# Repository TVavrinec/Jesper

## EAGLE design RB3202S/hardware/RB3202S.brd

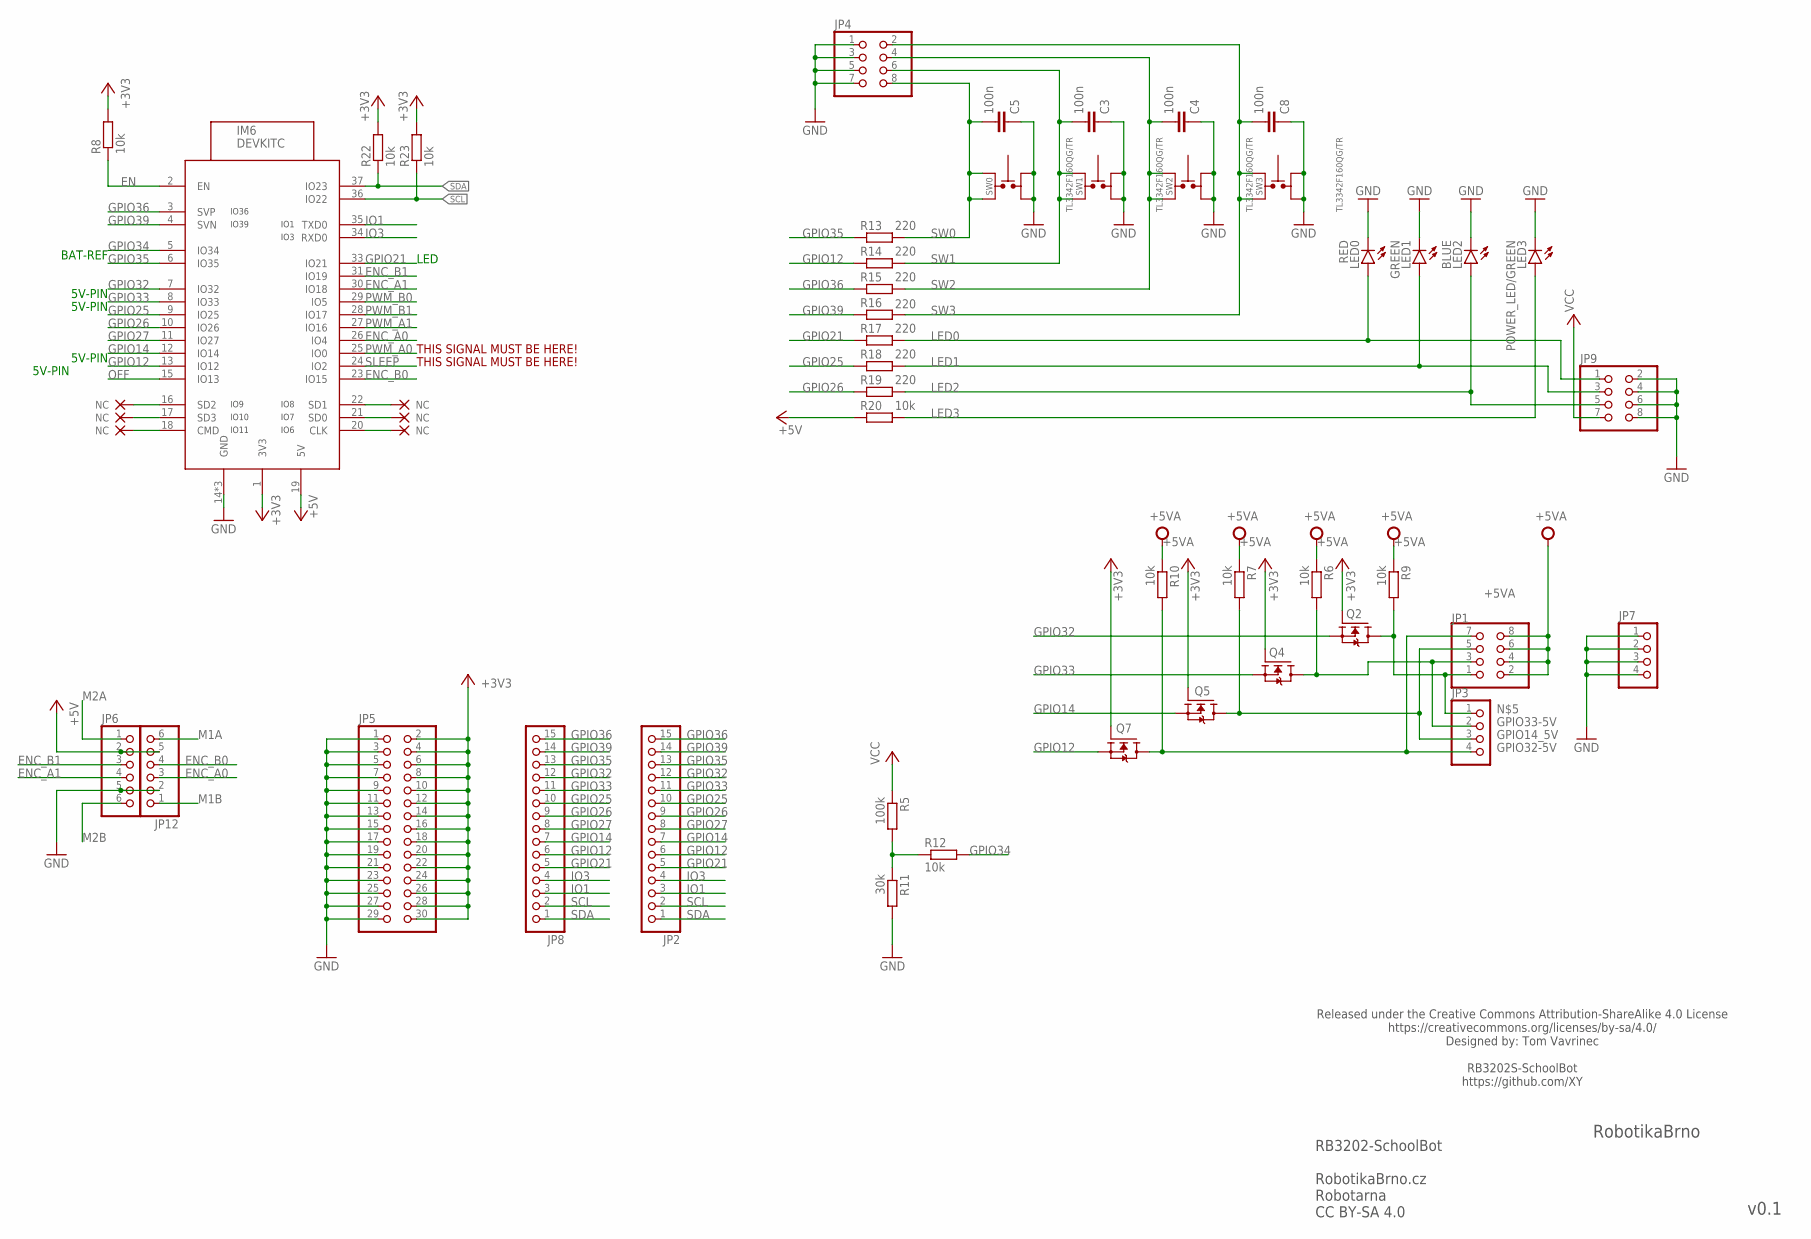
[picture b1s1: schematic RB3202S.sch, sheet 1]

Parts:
C3, C4, C5, C8: 100n; C0402
IM6: DEVKITC
JP1, JP4, JP9: PINHD-2X4; 2X04
JP2, JP8: PINHD-1X15; 1X15
JP3, JP7: PINHD-1X4; 1X04
JP5: PINHD-2X15; 2X15
JP6, JP12: PINHD-1X6; 1X06
LED0: RED; SML0603
LED1: GREEN; SML0603
LED2: BLUE; SML0603
LED3: POWER_LED/GREEN; SML0603
Q2, Q4, Q5, Q7: N-MOSFET-SOT23-GSD; SOT23
R5: 100k; R0402
R6, R7, R8, R9, R10, R12, R20, R22, R23: 10k; R0402
R11: 30k; R0402
R13, R14, R15, R16, R17, R18, R19: 220; R0402
SW0, SW1, SW2, SW3: TL3342F160QG/TR

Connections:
+3V3: IM6.1 (3V3), JP5.2, JP5.4, JP5.6, JP5.8, JP5.10, JP5.12, JP5.14, JP5.16, JP5.18, JP5.20, JP5.22, JP5.24, JP5.26, JP5.28, JP5.30, Q2.1 (G), Q4.1 (G), Q5.1 (G), Q7.1 (G), R8.2, R22.2, R23.2; also elsewhere on the board
+5V: IM6.19 (5V), JP6.2, JP12.5, R20.1; also elsewhere on the board
+5VA: JP1.2, JP1.4, JP1.6, JP1.8, R6.1, R7.1, R9.1, R10.1; also elsewhere on the board
EN: IM6.2 (EN), R8.1; also elsewhere on the board
ENC_A0: IM6.26 (IO4), JP12.3
ENC_A1: IM6.30 (IO18), JP6.4
ENC_B0: IM6.23 (IO15), JP12.4
ENC_B1: IM6.31 (IO19), JP6.3
GND: C3.1, C4.1, C5.1, C8.1, IM6.14 (GND), IM6.32 (GND), IM6.38 (GND), JP4.1, JP4.3, JP4.5, JP4.7, JP5.1, JP5.3, JP5.5, JP5.7, JP5.9, JP5.11, JP5.13, JP5.15, JP5.17, JP5.19, JP5.21, JP5.23, JP5.25, JP5.27, JP5.29, JP6.5, JP7.1, JP7.2, JP7.3, JP7.4, JP9.2, JP9.4, JP9.6, JP9.8, JP12.2, LED0.C, LED1.C, LED2.C, LED3.C, R11.2, SW0.1, SW0.2, SW1.1, SW1.2, SW2.1, SW2.2, SW3.1, SW3.2; also elsewhere on the board
GPIO12: IM6.13 (IO12), JP2.6, JP8.6, Q7.2 (S), R14.1
GPIO14: IM6.12 (IO14), JP2.7, JP8.7, Q5.2 (S)
GPIO14_5V: JP1.5, JP3.3, Q5.3 (D), R7.2
GPIO21: IM6.33 (IO21), JP2.5, JP8.5, R17.1; also elsewhere on the board
GPIO25: IM6.9 (IO25), JP2.10, JP8.10, R18.1
GPIO26: IM6.10 (IO26), JP2.9, JP8.9, R19.1
GPIO27: IM6.11 (IO27), JP2.8, JP8.8; also elsewhere on the board
GPIO32: IM6.7 (IO32), JP2.12, JP8.12, Q2.2 (S)
GPIO32-5V: JP1.7, JP3.4, Q7.3 (D), R10.2
GPIO33: IM6.8 (IO33), JP2.11, JP8.11, Q4.2 (S)
GPIO33-5V: JP1.3, JP3.2, Q4.3 (D), R6.2
GPIO34: IM6.5 (IO34), R12.2
GPIO35: IM6.6 (IO35), JP2.13, JP8.13, R13.1
GPIO36: IM6.3 (SVP), JP2.15, JP8.15, R15.1; also elsewhere on the board
GPIO39: IM6.4 (SVN), JP2.14, JP8.14, R16.1; also elsewhere on the board
IO1: IM6.35 (TXD0), JP2.3, JP8.3
IO3: IM6.34 (RXD0), JP2.4, JP8.4
IO9_NC: IM6.16 (SD2)
IO9_NC1: IM6.20 (CLK)
IO10_NC: IM6.17 (SD3)
IO10_NC1: IM6.21 (SD0)
IO11_NC: IM6.18 (CMD)
IO11_NC1: IM6.22 (SD1)
LED0: JP9.1, LED0.A, R17.2
LED1: JP9.3, LED1.A, R18.2
LED2: JP9.5, LED2.A, R19.2
LED3: LED3.A, R20.2
M1A: JP12.6; also elsewhere on the board
M1B: JP12.1; also elsewhere on the board
M2A: JP6.1; also elsewhere on the board
M2B: JP6.6; also elsewhere on the board
unnamed: R5.2, R11.1, R12.1
unnamed: JP1.1, JP3.1, Q2.3 (D), R9.2
OFF: IM6.15 (IO13); also elsewhere on the board
PWM_A0: IM6.25 (IO0); also elsewhere on the board
PWM_A1: IM6.27 (IO16); also elsewhere on the board
PWM_B0: IM6.29 (IO5); also elsewhere on the board
PWM_B1: IM6.28 (IO17); also elsewhere on the board
SCL: IM6.36 (IO22), JP2.2, JP8.2, R23.1; also elsewhere on the board
SDA: IM6.37 (IO23), JP2.1, JP8.1, R22.1; also elsewhere on the board
SLEEP: IM6.24 (IO2); also elsewhere on the board
SW0: C5.2, JP4.8, R13.2, SW0.3, SW0.4
SW1: C3.2, JP4.6, R14.2, SW1.3, SW1.4
SW2: C4.2, JP4.4, R15.2, SW2.3, SW2.4
SW3: C8.2, JP4.2, R16.2, SW3.3, SW3.4
VCC: JP9.7, R5.1; also elsewhere on the board

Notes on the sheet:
RB3202-SchoolBot RobotikaBrno.cz Robotarna CC BY-SA 4.0
RobotikaBrno
v0.1
Released under the Creative Commons Attribution-ShareAlike 4.0 License https://creativecommons.org/licenses/by-sa/4.0/ Designed by: Tom Vavrinec RB3202S-SchoolBot https://github.com/XY
THIS SIGNAL MUST BE HERE!
LED
5V-PIN
BAT-REF

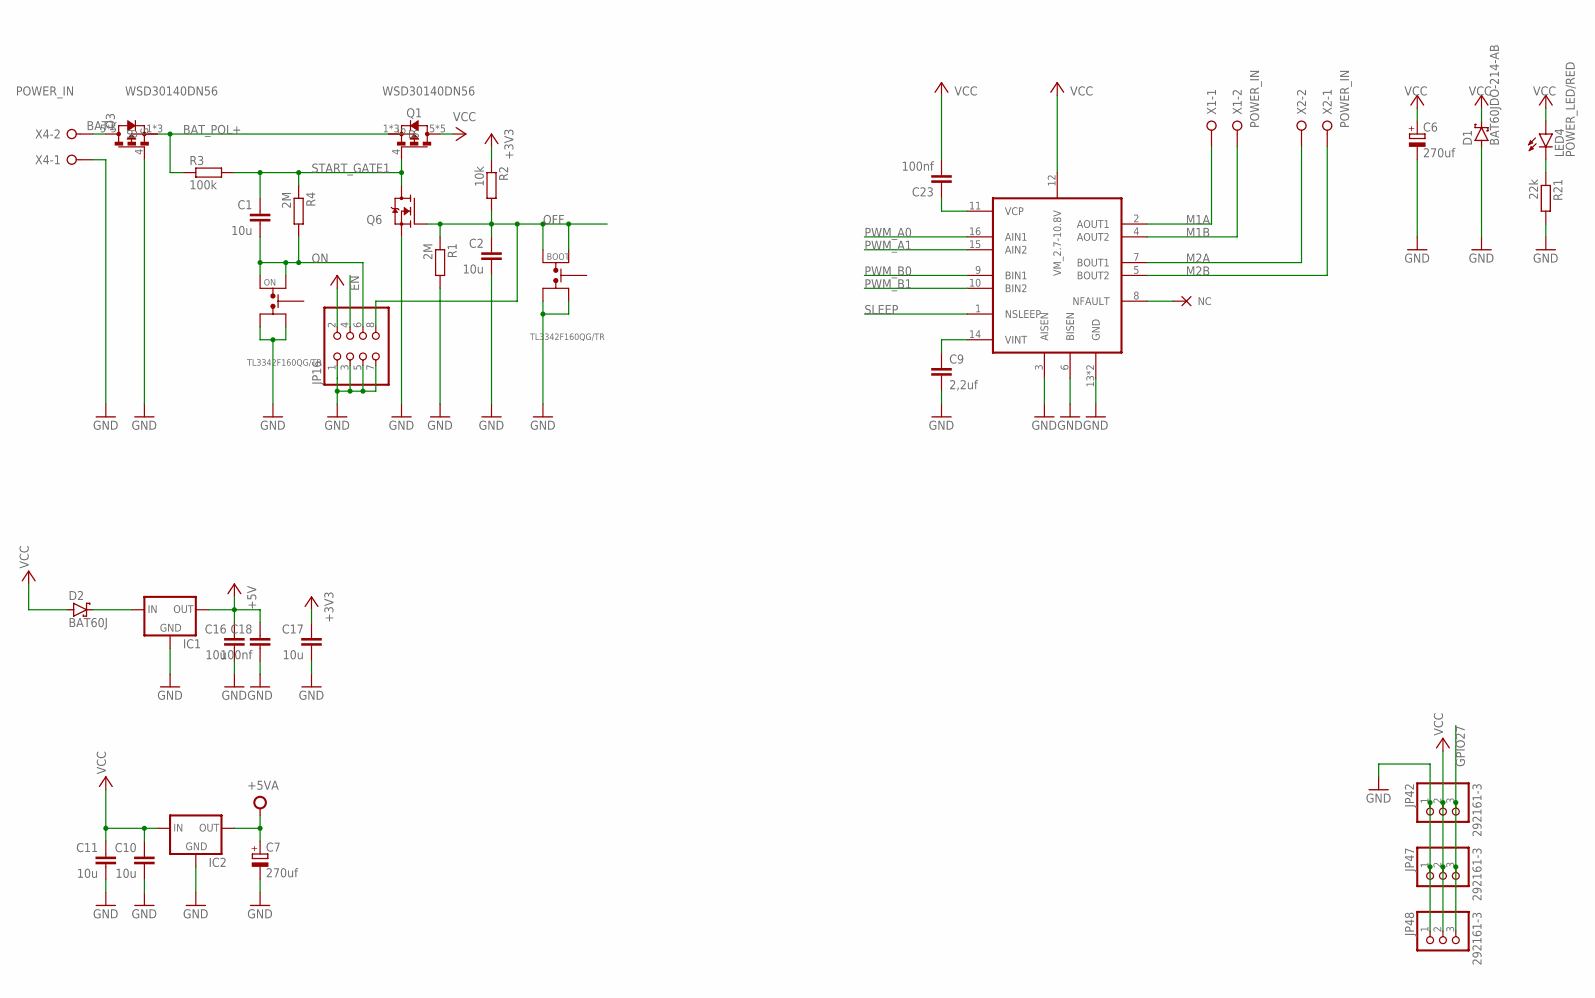
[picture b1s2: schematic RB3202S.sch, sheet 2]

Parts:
BOOT: TL3342F160QG/TR
C1, C2, C10, C11, C16, C17: 10u; C1206
C6, C7: 270uf; 140CLH-1010
C9: 2,2uf; C0805
C18: 100nf; C1206
C23: 100nf; C0402
D1: BAT60JDO-214-AB; DO214BA
D2: BAT60J; SOD323_ST
IC1, IC2: LM1117; SOT223
JP16: PINHD-2X4; 2X04
JP42, JP47, JP48: 292161-3
LED4: POWER_LED/RED; SML0603
ON: TL3342F160QG/TR
Q1, Q3: WSD30140DN56; DFN-8_EP_5.2X6.0X1.27P
Q6: N-MOSFET-SOT23-GSD; SOT23
R1, R4: 2M; R0402
R2: 10k; R0402
R3: 100k; R0402
R21: 22k; R0402
U$9: DRV8833CPWPR; SOP65P640X120-17N
X1, X2, X4: POWER_IN; W237-132

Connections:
+3V3: C17.1, R2.1; also elsewhere on the board
+5V: C16.1, C18.1, IC1.2 (OUT), IC1.4 (OUT), JP16.2; also elsewhere on the board
+5VA: C7.+, IC2.2 (OUT), IC2.4 (OUT); also elsewhere on the board
BAT1: Q3.5 (D), Q3.6 (D), Q3.7 (D), Q3.8 (D), Q3.9 (D), X4.2
BAT_POL+: Q1.1 (S), Q1.2 (S), Q1.3 (S), Q3.1 (S), Q3.2 (S), Q3.3 (S), R3.1
EN: JP16.4; also elsewhere on the board
GND: BOOT.1, BOOT.2, C2.2, C6.-, C7.-, C9.2, C10.2, C11.2, C16.2, C17.2, C18.2, D1.A, IC1.1 (GND), IC2.1 (GND), JP16.1, JP16.3, JP16.5, JP16.7, JP42.1, JP47.1, JP48.1, ON.1, ON.2, Q3.4 (G), Q6.2 (S), R1.2, R21.2, U$9.3 (AISEN), U$9.6 (BISEN), U$9.13 (GND), U$9.17 (GND), X4.1; also elsewhere on the board
GPIO27: JP42.3, JP47.3, JP48.3; also elsewhere on the board
IO9_NC2: U$9.8 (NFAULT)
M1A: U$9.2 (AOUT1), X1.1; also elsewhere on the board
M1B: U$9.4 (AOUT2), X1.2; also elsewhere on the board
M2A: U$9.7 (BOUT1), X2.2; also elsewhere on the board
M2B: U$9.5 (BOUT2), X2.1; also elsewhere on the board
unnamed: LED4.C, R21.1
unnamed: D2.C, IC1.3 (IN)
unnamed: C9.1, U$9.14 (VINT)
unnamed: C23.1, U$9.11 (VCP)
OFF: BOOT.3, BOOT.4, C2.1, JP16.8, Q6.1 (G), R1.1, R2.2; also elsewhere on the board
ON: C1.2, JP16.6, ON.3, ON.4, R4.2
PWM_A0: U$9.16 (AIN1); also elsewhere on the board
PWM_A1: U$9.15 (AIN2); also elsewhere on the board
PWM_B0: U$9.9 (BIN1); also elsewhere on the board
PWM_B1: U$9.10 (BIN2); also elsewhere on the board
SLEEP: U$9.1 (NSLEEP); also elsewhere on the board
START_GATE1: C1.1, Q1.4 (G), Q6.3 (D), R3.2, R4.1
VCC: C6.+, C10.1, C11.1, C23.2, D1.C, D2.A, IC2.3 (IN), JP42.2, JP47.2, JP48.2, LED4.A, Q1.5 (D), Q1.6 (D), Q1.7 (D), Q1.8 (D), Q1.9 (D), U$9.12 (VM_2.7-10.8V); also elsewhere on the board

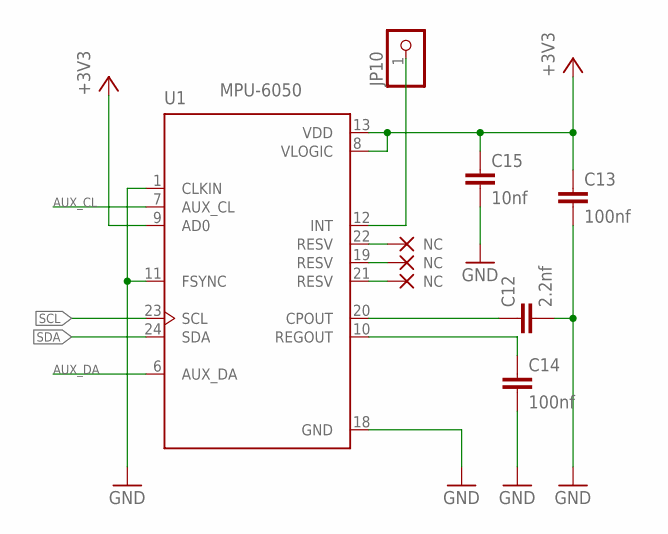
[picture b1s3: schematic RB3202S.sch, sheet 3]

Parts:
C12: 2.2nf; C0402
C13: 100nf; C0402
C14: 100nf; C0402P
C15: 10nf; C0402
JP10: PINHD-1X1; 1X01
U1: MPU-6050; QFN50P400X400X95-24N

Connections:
+3V3: C13.1, C15.1, U1.8 (VLOGIC), U1.9 (AD0), U1.13 (VDD); also elsewhere on the board
AUX_CL: U1.7 (AUX_CL)
AUX_DA: U1.6 (AUX_DA)
GND: C12.2, C13.2, C14.2, C15.2, U1.1 (CLKIN), U1.11 (FSYNC), U1.18 (GND); also elsewhere on the board
INT_MPU5060: JP10.1, U1.12 (INT)
IO9_NC4: U1.19 (RESV)
IO9_NC5: U1.21 (RESV)
IO10_NC4: U1.22 (RESV)
unnamed: C12.1, U1.20 (CPOUT)
unnamed: C14.1, U1.10 (REGOUT)
SCL: U1.23 (SCL); also elsewhere on the board
SDA: U1.24 (SDA); also elsewhere on the board

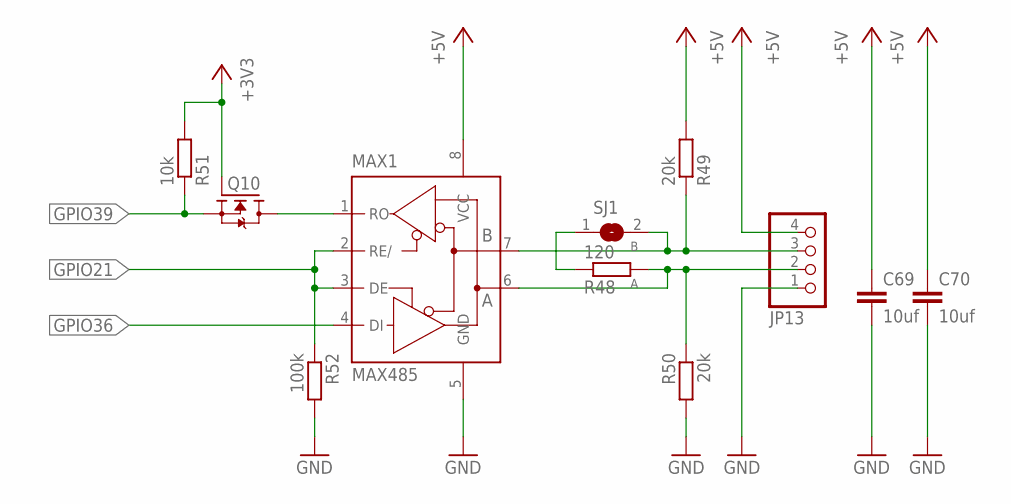
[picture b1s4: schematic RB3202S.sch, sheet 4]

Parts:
C69, C70: 10uf; C0805
JP13: PINHD-1X4; 1X04
MAX1: MAX485; SO08
Q10: N-MOSFET-SOT23-GSD; SOT23
R48: 120; R0402
R49, R50: 20k; R0402
R51: 10k; R0402
R52: 100k; R0402
SJ1: SJ

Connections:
+3V3: Q10.1 (G), R51.2; also elsewhere on the board
+5V: C69.1, C70.1, JP13.4, MAX1.8 (VCC), R49.2; also elsewhere on the board
A: JP13.2, MAX1.6 (A), R48.2, R50.1
B: JP13.3, MAX1.7 (B), R49.1, SJ1.2
GND: C69.2, C70.2, JP13.1, MAX1.5 (GND), R50.2, R52.2; also elsewhere on the board
GPIO21: MAX1.2 (RE/), MAX1.3 (DE), R52.1; also elsewhere on the board
GPIO36: MAX1.4 (DI); also elsewhere on the board
GPIO39: Q10.2 (S), R51.1; also elsewhere on the board
unnamed: R48.1, SJ1.1
RX-485-5V: MAX1.1 (RO), Q10.3 (D)

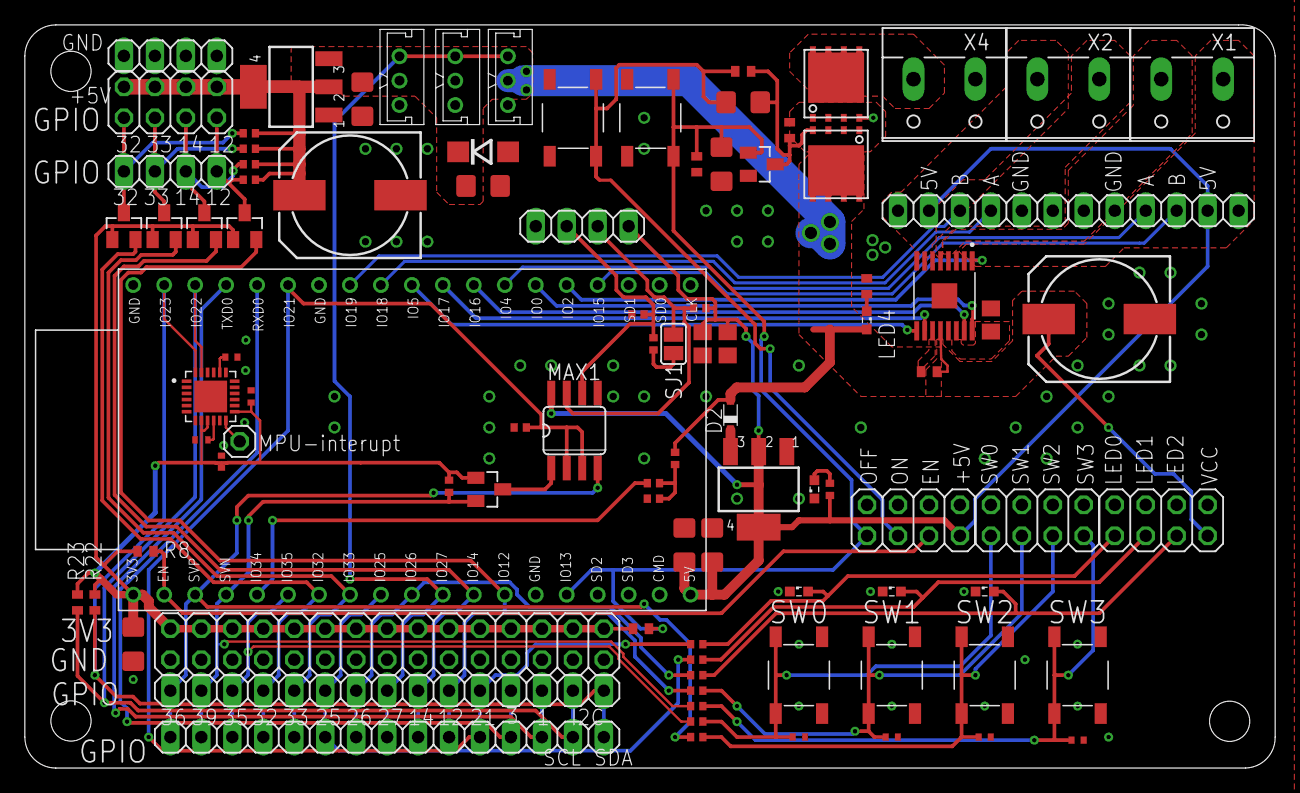
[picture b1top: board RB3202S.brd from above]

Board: 2 copper layers, 102.6 x 61.0 mm, 96 parts (0 on the bottom side), 64 nets.

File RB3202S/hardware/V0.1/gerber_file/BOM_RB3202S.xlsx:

Comment | Designator | Footprint | LCSC Part #（optional）
 | IC1, IC2 | SOT-223 | C134077
270uf | C6, C7 | SMD-ECAP-10x10 | C311670
100nf | C3, C4, C5, C8, C13, C14, C20, C21, C23 | 0402_C | C1525
10uf | C1, C2, C10, C11, C16, C17 | 1206_C | C89632
10uf | C69, C70 | 0805_C | C15850
2.2uf | C9 | 0805_C | C49217
2.2nf | C12 | 0402_C | C1531
220nf | C18 | 0402_C | C16772
4.7uf | C19 | 0805_C | C1779
10nf | C15 | 0402_C | C15195
 | D1 | DO214BA | C110482
 | LED0, LED4 | LED_0603 | C2286
 | LED2, LED3 | LED_0603 | C72043
 | LED1 | LED_0603 | C72038
 | SW0, SW1, SW2, SW3, ON, BOOT | TL3342F160QG/TR | C318887
 | Q1, Q3 | AO3401ASOP-8_EP_5.0X5.0X1.27P | C180399
 | Q2, Q4, Q5, Q6, Q7, Q10 | SOT-23-3 | C122850
 | U$9 | HTSSOP-16_EP_4.4x5.0x0.65P | C50506
 | U1 | QFN-24_EP_4.0x4.0x0.5P | C24112
1M | R1, R4 | 0402_R | C26083
10k | R2, R6, R7, R8, R9, 10, R12, R22, R23, R51 | 0402_R | C25744
100k | R3, R52 | 0402_R | C25741
100k | R5, R49 | 0402_R | C25741
30k | R11, R50 | 0402_R | C105614
120 | R48 | 0402_R | C25079
220 | R13-19 | 0402_R | C25092
1k | R20, R21 | 0402_R | C11702
 | IC3 | LGA-16_3x3x0.5P | C192585
 | MAX1 | SOIC-8_3.9x4.9x1.27P | C9945

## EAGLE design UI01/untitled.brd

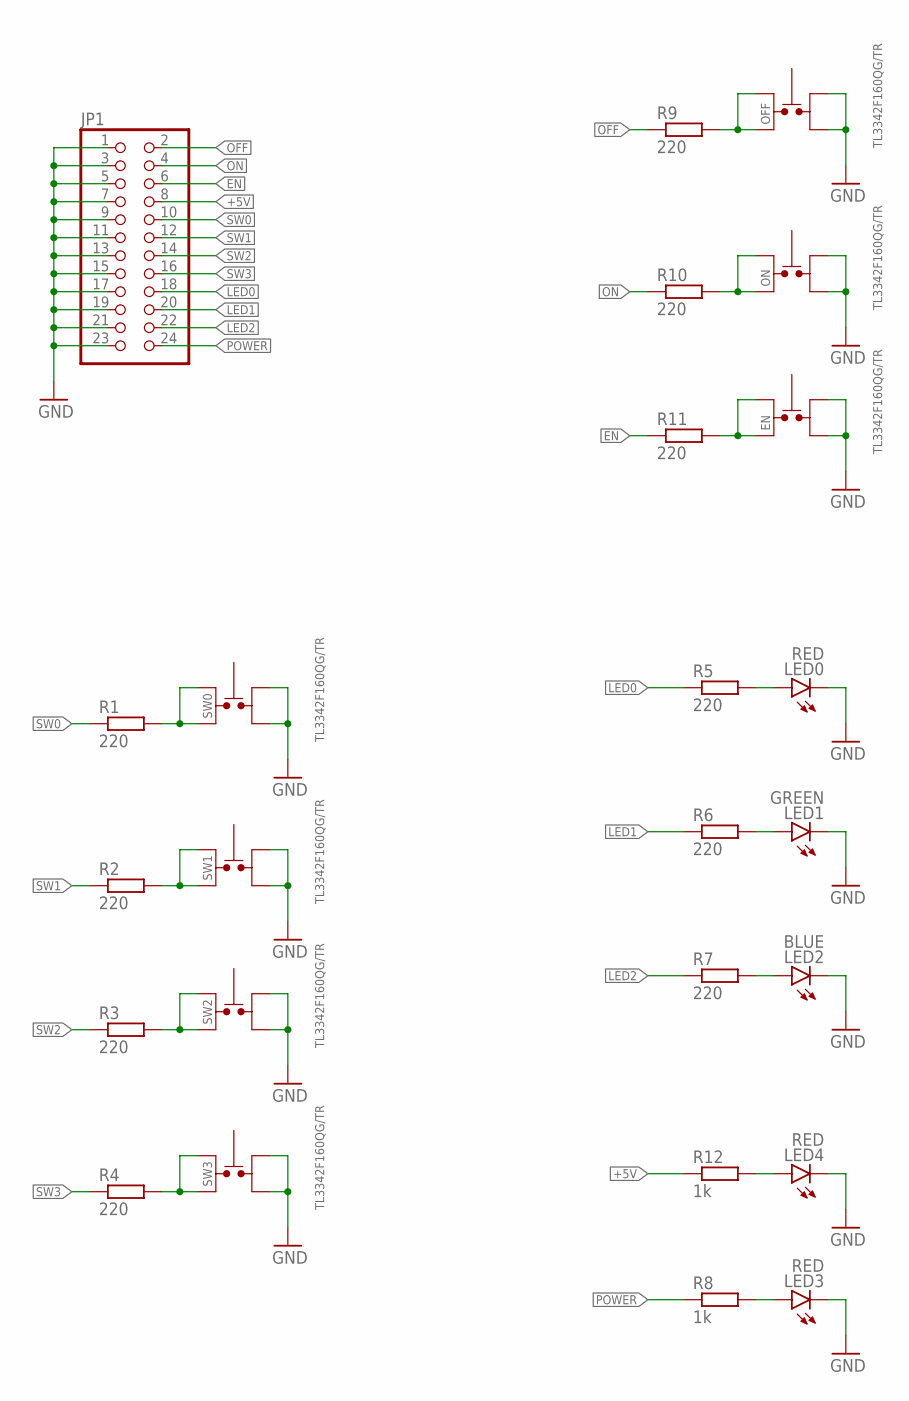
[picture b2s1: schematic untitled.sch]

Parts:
EN: TL3342F160QG/TR
JP1: PINHD-2X12; 2X12
LED0, LED3, LED4: RED; SML0603
LED1: GREEN; SML0603
LED2: BLUE; SML0603
OFF: TL3342F160QG/TR
ON: TL3342F160QG/TR
R1, R2, R3, R4, R5, R6, R7, R9, R10, R11: 220; R0402
R8, R12: 1k; R0402
SW0, SW1, SW2, SW3: TL3342F160QG/TR

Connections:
+5V: JP1.8, R12.1
EN: JP1.6, R11.1
GND: EN.1, EN.2, JP1.1, JP1.3, JP1.5, JP1.7, JP1.9, JP1.11, JP1.13, JP1.15, JP1.17, JP1.19, JP1.21, JP1.23, LED0.C, LED1.C, LED2.C, LED3.C, LED4.C, OFF.1, OFF.2, ON.1, ON.2, SW0.1, SW0.2, SW1.1, SW1.2, SW2.1, SW2.2, SW3.1, SW3.2
LED0: JP1.18, R5.1
LED1: JP1.20, R6.1
LED2: JP1.22, R7.1
unnamed: R1.2, SW0.3, SW0.4
unnamed: R2.2, SW1.3, SW1.4
unnamed: R3.2, SW2.3, SW2.4
unnamed: R4.2, SW3.3, SW3.4
unnamed: LED0.A, R5.2
unnamed: LED1.A, R6.2
unnamed: LED2.A, R7.2
unnamed: LED3.A, R8.2
unnamed: OFF.3, OFF.4, R9.2
unnamed: ON.3, ON.4, R10.2
unnamed: EN.3, EN.4, R11.2
unnamed: LED4.A, R12.2
OFF: JP1.2, R9.1
ON: JP1.4, R10.1
POWER: JP1.24, R8.1
SW0: JP1.10, R1.1
SW1: JP1.12, R2.1
SW2: JP1.14, R3.1
SW3: JP1.16, R4.1

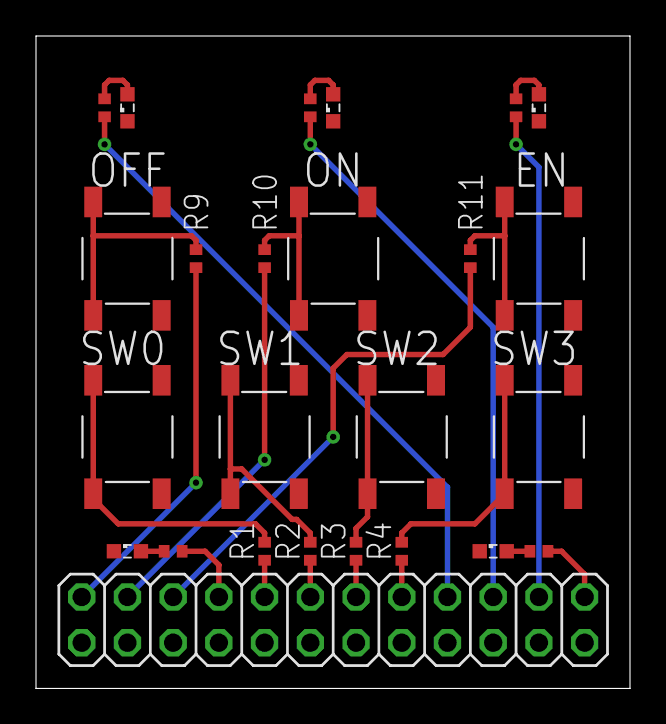
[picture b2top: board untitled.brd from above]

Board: 2 copper layers, 33.0 x 36.2 mm, 25 parts (0 on the bottom side), 25 nets.

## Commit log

2020-02-18 zaroutovana_deska
2020-02-20 kompas_navic
2020-03-01 loga
2020-03-10 BlackBox standard
2020-03-14 oprava ledek
2020-03-15 predelavka na ESP-IDF
2020-03-17 esp-idf
2020-05-02 dataasheety
2020-05-02 novi tranzistor do knihovny
    JLCPCB neměli ten starý na skladě tak jsem potřeboval jiný ale neměli ho ve stejném pouzdře tak jsem musel použít jiné
2020-05-02 zarazeni verze do jmena
2020-05-02 logo
2020-05-02 cisteni + gitignore
2020-05-02 aktualni nazvy
2020-05-02 nove logo
2020-05-02 libraris
2020-05-02 vyrova
    vytvoreni slozky pro verzi 0.2
2020-05-02 aktualni eagle soubory
    pro dalsi upravu

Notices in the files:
parts and their libraries:
esp32: Creative Commons Attribution-ShareAlike 4.0 International
